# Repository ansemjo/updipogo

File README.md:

# updipogo

This was an idea to combine a tiny board with [pogo pins](https://aliexpress.com/item/1005002667659397.html) (spring-loaded probes) on one end and a cheap [CH340N USB-to-UART chip](https://lcsc.com/product-detail/USB-ICs_WCH-Jiangsu-Qin-Heng-CH340N_C2977777.html) on the other end, to build an [UPDI programmer](https://github.com/SpenceKonde/AVR-Guidance/blob/master/UPDI/jtag2updi.md). The idea stems from a [Pnoxi AVR-ISP Pogo](https://www.tindie.com/products/pnoxi/avr-isp-pogo-pin-adapter-2x3-idc2x3-pogo-254mm/), which I use for programming older AVRs.

**Note:** It may be worthwhile to replace the 4.7 kΩ resistor with a diode instead. Or at least, use a smaller resistor in the range of 1–2 kΩ. [See errata](ERRATA.md#updipogo_v2).

### Programming Pads

The pogo footprint uses a somewhat dense pitch of 1.6 mm so that programming pads on future boards could require minimal space. The underside has footprints to add pins with standard 2.54 mm pitch or even a "normal" header, though.

Add small 0.4 mm vias in the middle of the three programming pads if you can to give the spearhead tips something to fall into.

### Make Your Own

* Install [`kikit`](https://github.com/yaqwsx/KiKit)
* Run `make gerbers.zip`
* Order your PCBs
* Check the [interactive BOM](https://htmlpreview.github.io/?https://github.com/ansemjo/updipogo/blob/main/ibom.html) to see which part goes where

### Alternatives

[Stefan Wagner lists a lot of possible UPDI programmer alternatives](https://github.com/wagiminator/AVR-Programmer). Those include voltage switching, HV capable programmers and `jtag2updi`-compatible ones.

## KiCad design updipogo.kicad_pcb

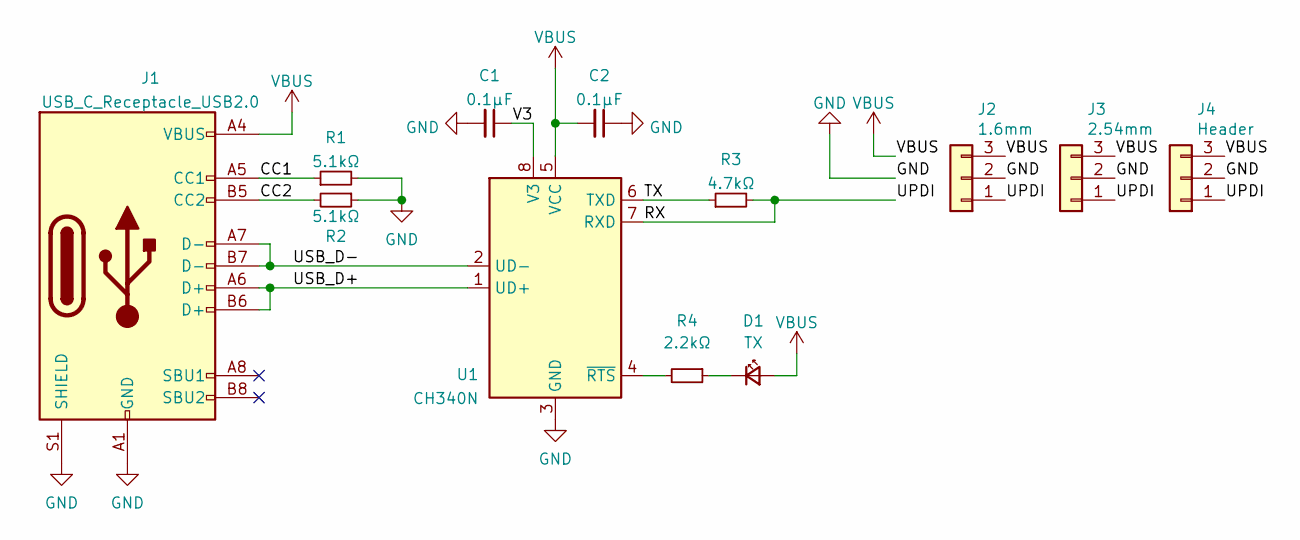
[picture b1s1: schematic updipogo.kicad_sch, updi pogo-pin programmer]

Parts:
C1, C2: 0.1µF; C_0805_2012Metric_Pad1.18x1.45mm_HandSolder
D1: TX; LED_0805_2012Metric_Pad1.15x1.40mm_HandSolder
J1: USB_C_Receptacle_USB2.0; USB_C_Receptacle_HRO_TYPE-C-31-M-12
J2: 1.6mm; PogoPins_1.6mm
J3: 2.54mm; PogoPins_2.54mm
J4: Header; CustomPinHeader_1x03_P2.54mm_Horizontal
R1, R2: 5.1kΩ; R_0805_2012Metric_Pad1.20x1.40mm_HandSolder
R3: 4.7kΩ; R_0805_2012Metric_Pad1.20x1.40mm_HandSolder
R4: 2.2kΩ; R_0805_2012Metric_Pad1.20x1.40mm_HandSolder
U1: CH340N; SOP-8_3.9x4.9mm_P1.27mm

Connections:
/CC1: J1.A5 (CC1), R1.1
/CC2: J1.B5 (CC2), R2.2
/RX: J2.1, J3.1, J4.1, R3.2, U1.7 (RXD)
/TX: R3.1, U1.6 (TXD)
/USB_D+: J1.A6 (D+), J1.B6 (D+), U1.1 (UD+)
/USB_D-: J1.A7 (D-), J1.B7 (D-), U1.2 (UD-)
/V3: C1.1, U1.8 (V3)
GND: C1.2, C2.1, J1.A1 (GND), J1.A12 (GND), J1.B1 (GND), J1.B12 (GND), J1.S1 (SHIELD), J2.2, J3.2, J4.2, R1.2, R2.1, U1.3 (GND)
unnamed: D1.1 (K), R4.1
unnamed: R4.2, U1.4 (~RTS)
VBUS: C2.2, D1.2 (A), J1.A4 (VBUS), J1.A9 (VBUS), J1.B4 (VBUS), J1.B9 (VBUS), J2.3, J3.3, J4.3, U1.5 (VCC)

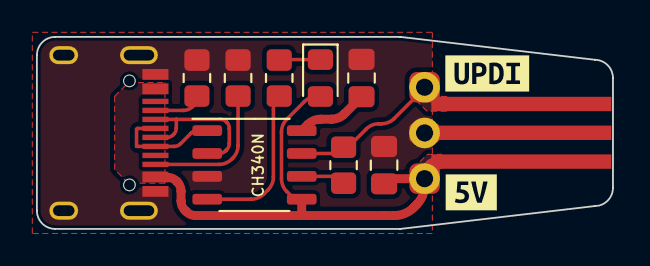
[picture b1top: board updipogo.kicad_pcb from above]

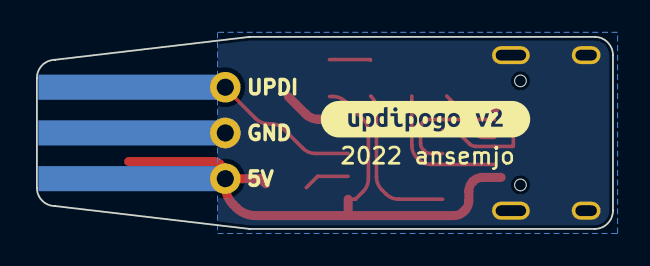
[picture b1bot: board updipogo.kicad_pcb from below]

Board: 2 copper layers, 32.0 x 10.7 mm, 15 parts (3 on the bottom side), 11 nets.

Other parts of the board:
kibuzzard-630501DC: G***; kibuzzard-630501DC
kibuzzard-6305024E: G***; kibuzzard-6305024E
kibuzzard-6305027C: G***; kibuzzard-6305027C

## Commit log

2021-08-29 commit v1 of finished updipogo idea
2021-08-29 add readme with render
2021-08-29 add tusk.yml with kikit tasks
2021-08-29 handcrafted 2x6 panel for jlcpcb
2021-09-18 change pinout of pogo pins to avoid rev. polarity danger
2021-09-18 update pcb for new pinout
2021-09-19 reverse pin numbering and add footprint for pads
    updi pin is now pin 1 and is square / boxed-in on programming pads
    footprint
2021-09-19 change milling radius on tip narrowing
2021-09-29 fix usb polarity
2021-10-12 add note about lit-up LED
2021-10-12 fix a few things in readme, added picture of botched first rev
2021-10-22 add more photos, note in readme about error
2022-08-23 connect led to RTS and update pcb layout a bit
2022-08-23 update footprints from library for new 3d model paths
2022-08-23 update panelization and fab, use makefile
2022-09-21 add interactive bom
2022-09-21 update readme and add v2 images
2022-09-21 add link to alternatives
2022-09-21 add instructions to readme
2022-09-22 add errata about switching resistor for diode
2022-09-22 fix malformed link
2022-10-09 add image for v2 diode errata
2022-10-09 fix ibom link in readme
